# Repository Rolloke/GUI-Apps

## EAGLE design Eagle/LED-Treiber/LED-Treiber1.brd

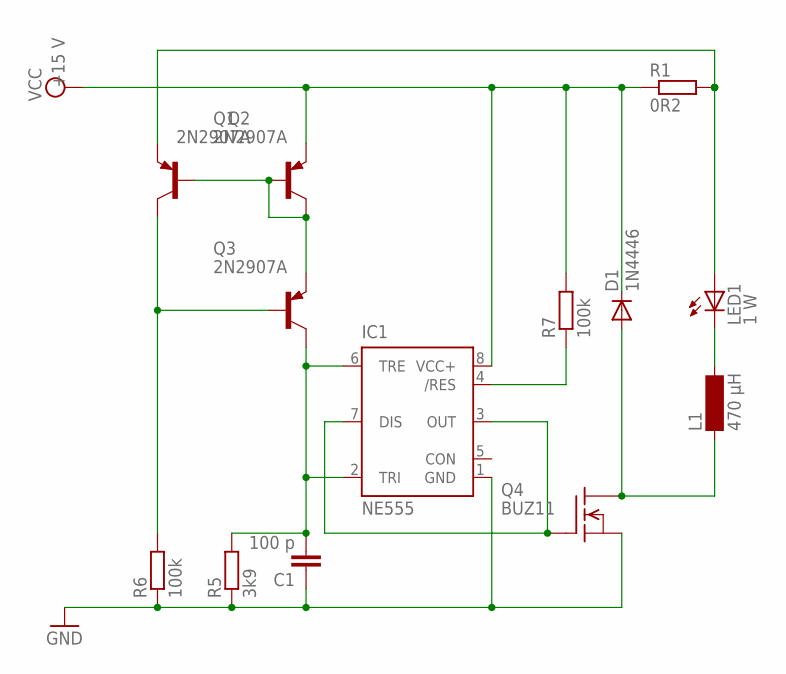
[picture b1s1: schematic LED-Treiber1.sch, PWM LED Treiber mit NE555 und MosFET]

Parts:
C1: 100 p; C2.5-3
D1: 1N4446; DO35-10
IC1: NE555; DIL-08
L1: 470 µH; MS85
LED1: 1 W; LED5MM
Q1, Q2, Q3: 2N2907A; TO18
Q4: BUZ11; TO220
R1: 0R2; 0207/10
R5: 3k9; 0207/10
R6, R7: 100k; 0207/10

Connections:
GND: C1.1, IC1.1 (GND), Q4.3 (S), R5.1, R6.1
unnamed: Q1.2 (B), Q1.3 (C), Q2.2 (B), Q3.1 (E)
unnamed: C1.2, IC1.2 (TRI), IC1.6 (TRE), Q3.3 (C), R5.2
unnamed: Q2.3 (C), Q3.2 (B), R6.2
unnamed: IC1.3 (OUT), IC1.7 (DIS), Q4.1 (G)
unnamed: IC1.4 (/RES), R7.1
unnamed: D1.A, L1.1, Q4.2 (D)
unnamed: L1.2, LED1.K (C)
unnamed: LED1.A, Q2.1 (E), R1.2
VCC: D1.C, IC1.8 (VCC+), Q1.1 (E), R1.1, R7.2

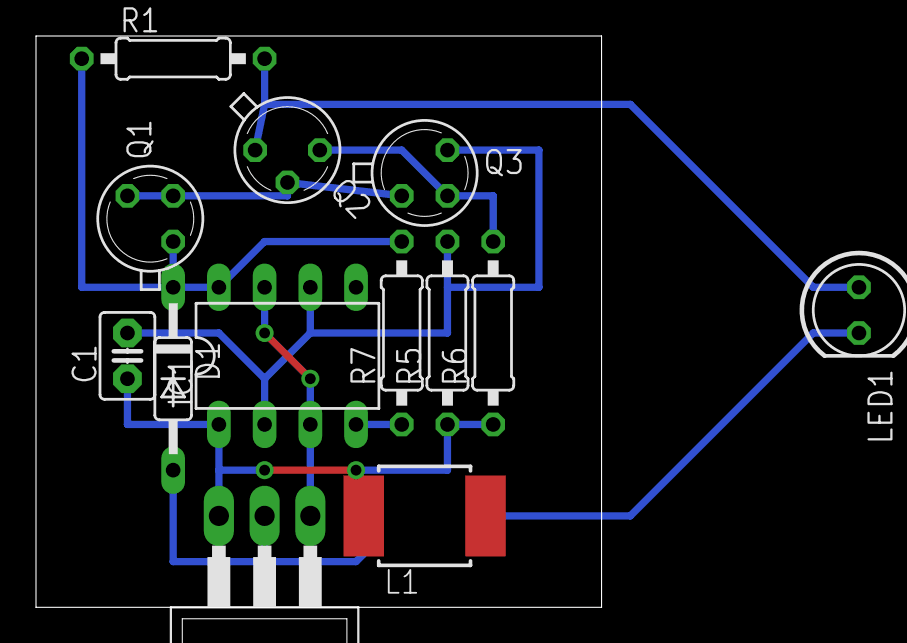
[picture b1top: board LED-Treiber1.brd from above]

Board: 2 copper layers, 31.4 x 31.7 mm, 13 parts (0 on the bottom side), 10 nets.

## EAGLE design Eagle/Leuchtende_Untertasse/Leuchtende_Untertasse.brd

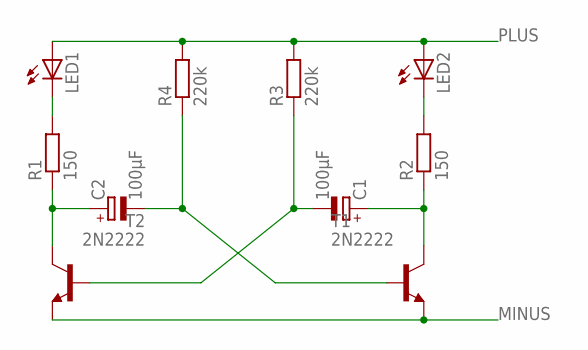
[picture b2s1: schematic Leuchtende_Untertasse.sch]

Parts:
C1, C2: 100µF; E2,5-5
LED1, LED2: LED5MM
R1, R2: 150; 0204/7
R3, R4: 220k; 0204/7
T1, T2: 2N2222; TO18

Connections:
MINUS: T1.1 (E), T2.1 (E)
unnamed: C2.+, R1.1, T2.3 (C)
unnamed: C1.+, R2.1, T1.3 (C)
unnamed: C1.-, R3.1, T2.2 (B)
unnamed: C2.-, R4.1, T1.2 (B)
unnamed: LED2.K (C), R2.2
unnamed: LED1.K (C), R1.2
PLUS: LED1.A, LED2.A, R3.2, R4.2

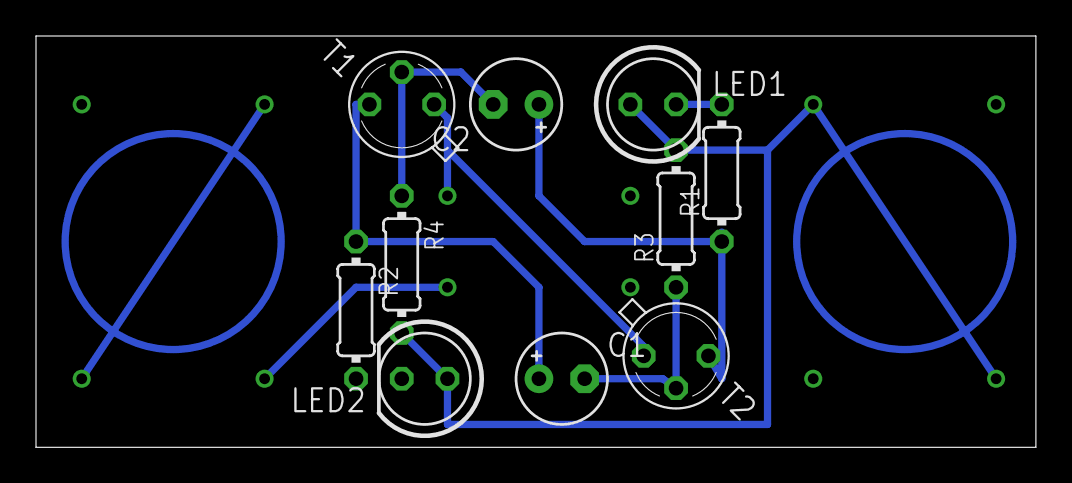
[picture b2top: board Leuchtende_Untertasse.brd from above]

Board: 2 copper layers, 55.5 x 22.8 mm, 10 parts (0 on the bottom side), 8 nets.

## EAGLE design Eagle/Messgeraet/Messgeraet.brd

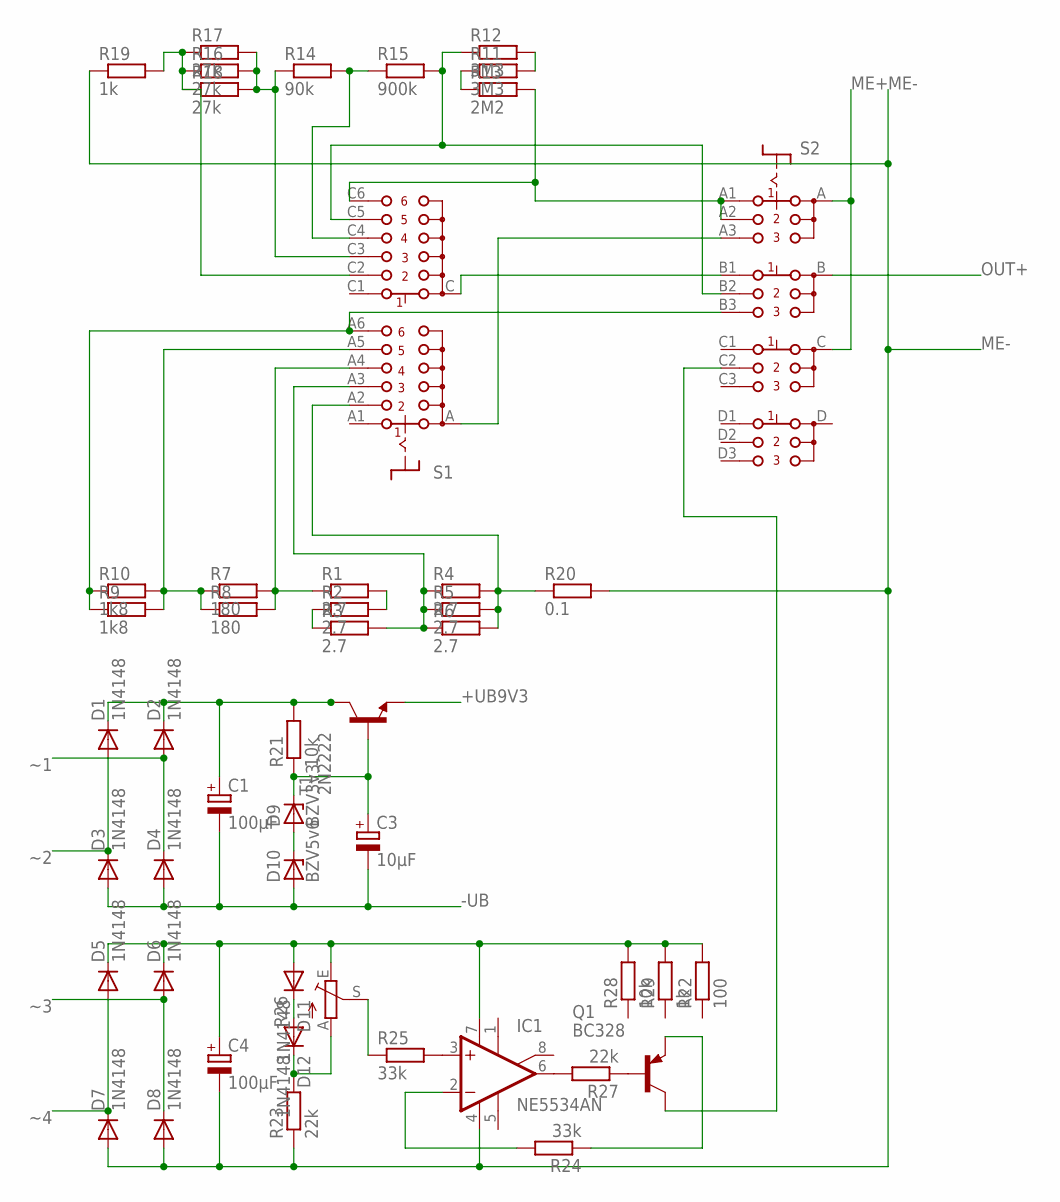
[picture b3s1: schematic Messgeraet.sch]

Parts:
C1, C4: 100µF; E5-10,5
C3: 10µF; E5-10,5
D1, D2, D3, D4, D5, D6, D7, D8, D11, D12: 1N4148; DO35-7
D9: BZV3v3; DO34Z7
D10: BZV5v6; DO34Z7
IC1: NE5534AN; DIL08
Q1: BC328; TO92-EBC
R1, R2, R3, R4, R5, R6: 2.7; 0617/17
R7, R8: 180; 0309/12
R9, R10: 1k8; 0309/10
R11, R12: 3M3; 0309/12
R13: 2M2; 0411/15
R14: 90k; 0411/15
R15: 900k; 0309V
R16, R17, R18: 27k; 0309/12
R19, R29: 1k; 0309/10
R20: 0.1; VTA52
R21, R28: 10k; 0309/10
R22: 100; 0309/10
R23, R27: 22k; 0309/10
R24, R25: 33k; 0309/10
R26: TRIM_EU-RJ9W; RJ9W
S1: CK102X06
S2: CK104X03
T1: 2N2222; TO18

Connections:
+UB9V3: T1.1 (E)
-UB: C1.-, C3.-, D3.A, D4.A, D10.A
ME+: S2.A, S2.C
ME-: C4.-, D7.A, D8.A, IC1.4 (V-), R19.1, R20.2, R23.1
unnamed: R7.1, R8.1, R9.2, R10.2, S1.A5
unnamed: S1.A, S2.A3
unnamed: R1.1, R7.2, R8.2, S1.A4
unnamed: R9.1, R10.1, S1.A6, S2.B3
unnamed: R1.2, R2.2
unnamed: R2.1, R3.1
unnamed: R3.2, R4.1, R5.1, R6.1, S1.A3
unnamed: R4.2, R5.2, R6.2, R20.1, S1.A2
unnamed: R14.1, R16.2, R17.2, R18.2, S1.C3
unnamed: R16.1, R17.1, R18.1, R19.2, S1.C2
unnamed: D12.C, R23.2, R26.A
unnamed: R14.2, R15.1, S1.C4
unnamed: R12.1, R15.2, S1.C5, S2.B2
unnamed: R11.2, R12.2
unnamed: R11.1, R13.1
unnamed: R13.2, S1.C6, S2.A1, S2.A2
unnamed: S1.C, S2.B1
unnamed: Q1.C, S2.C2
unnamed: IC1.6 (OUT), R27.2
unnamed: C1.+, D1.C, D2.C, R21.2, T1.3 (C)
unnamed: Q1.B, R27.1
unnamed: D11.C, D12.A
unnamed: Q1.E, R24.1
unnamed: C4.+, D5.C, D6.C, D11.A, IC1.7 (V+), R22.2, R26.E, R28.2, R29.2
unnamed: R25.1, R26.S
unnamed: D9.A, D10.C
unnamed: C3.+, D9.C, R21.1, T1.2 (B)
unnamed: IC1.2 (-IN), R24.2
unnamed: IC1.3 (+IN), R25.2
OUT+: S2.B
~1: D2.A, D4.C
~2: D1.A, D3.C
~3: D6.A, D8.C
~4: D5.A, D7.C

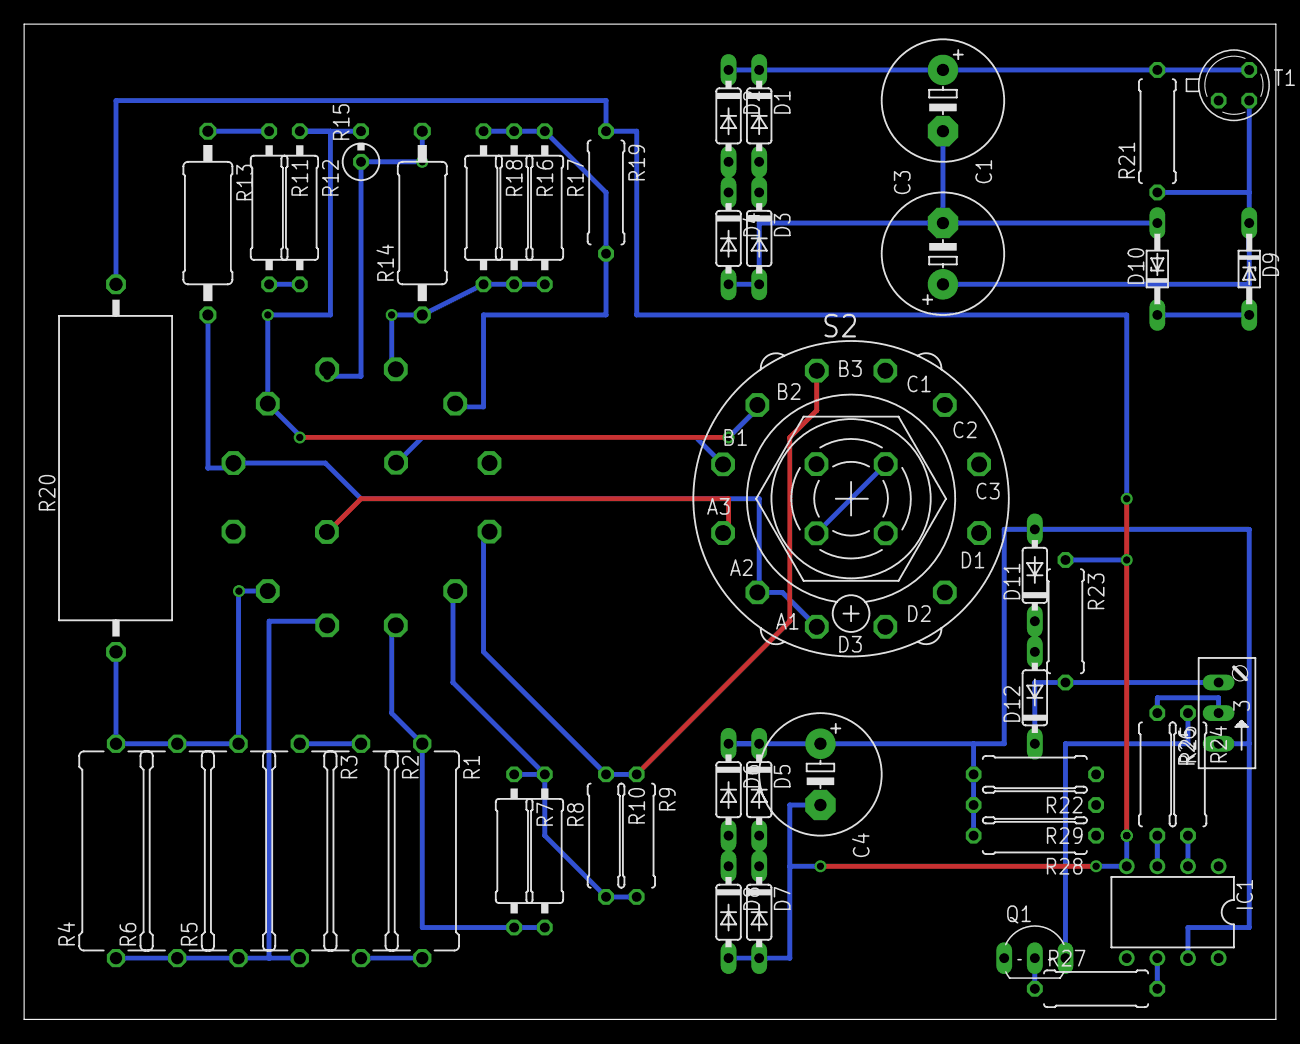
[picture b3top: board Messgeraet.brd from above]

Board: 2 copper layers, 103.8 x 82.5 mm, 49 parts (1 on the bottom side), 36 nets.

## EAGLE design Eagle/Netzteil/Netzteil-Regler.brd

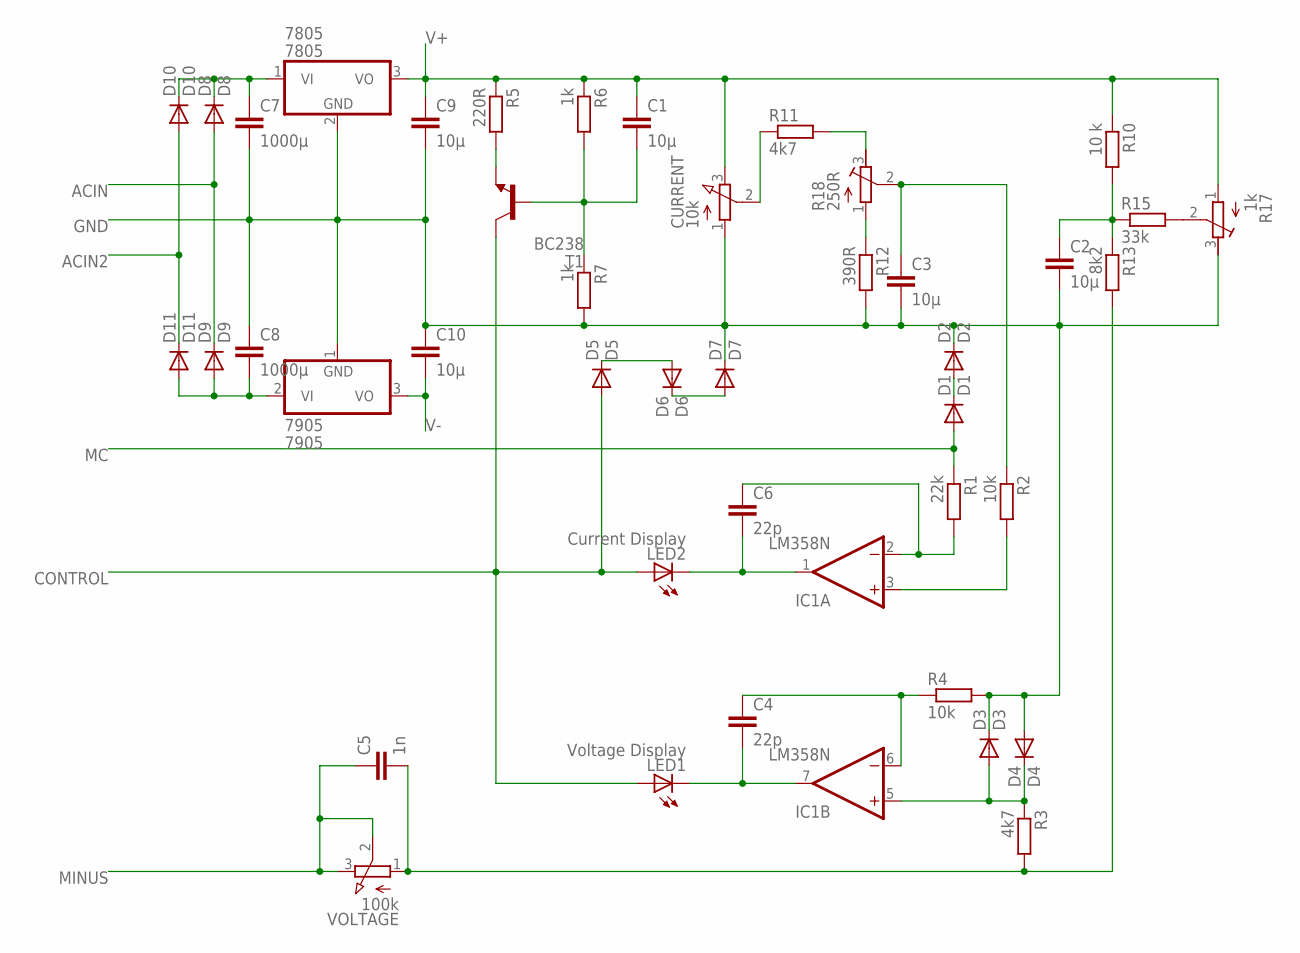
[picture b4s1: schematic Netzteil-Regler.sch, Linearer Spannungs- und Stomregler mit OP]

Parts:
7805: 7805; TO220V
7905: 7905; TO220V
C1, C2, C3, C9, C10: 10µ; C2.5-5
C4, C6: 22p; C5B4.5
C5: 1n; C5B4.5
C7, C8: 1000µ; C10B6
CURRENT: 10k; 3RP/1610N
D1: D1; DO35-10
D2: D2; DO35-10
D3: D3; DO35-10
D4: D4; DO35-10
D5: D5; DO35-10
D6: D6; DO35-10
D7: D7; DO35-10
D8: D8; DO41-10
D9: D9; DO41-10
D10: D10; DO41-10
D11: D11; DO41-10
IC1: LM358N; DIL08
LED1: Voltage Display; LED5MM
LED2: Current Display; LED5MM
R1: 22k; 0207/10
R2, R4: 10k; 0207/10
R3, R11: 4k7; 0207/10
R5: 220R; 0207/10
R6, R7: 1k; 0207/10
R10: 10 k; 0207/10
R12: 390R; 0207/10
R13: 8k2; 0207/10
R15: 33k; 0207/10
R17: 1k; RTRIM3296W
R18: 250R; RTRIM3296W
T1: BC238; TO92-CBE
VOLTAGE: 100k; 3RP/1610N

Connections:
ACIN: D8.A, D9.C
ACIN2: D10.A, D11.C
B: C1.2, R6.2, R7.1, T1.B
CONTROL: D5.A, LED1.A, LED2.A, T1.C
E: R5.2, T1.E
GND: 7805.2 (GND), 7905.1 (GND), C2.2, C3.2, C7.2, C8.1, C9.2, C10.1, CURRENT.1 (A), D2.C, D3.C, D4.A, D7.C, R4.2, R7.2, R12.2, R17.3 (A)
MC: D1.A, R1.1
MINUS: C5.1, VOLTAGE.2 (S), VOLTAGE.3 (E)
unnamed: R11.2, R18.3 (A)
unnamed: C3.1, R2.1, R18.2 (S)
unnamed: R12.1, R18.1 (E)
unnamed: D1.C, D2.A
unnamed: C2.1, R10.2, R13.1, R15.1
unnamed: CURRENT.2 (S), R11.1
unnamed: R15.2, R17.2 (S)
unnamed: IC1.3 (+IN), R2.2
unnamed: C6.1, IC1.2 (-IN), R1.2
unnamed: 7805.1 (VI), C7.1, D8.C, D10.C
unnamed: D5.C, D6.A
unnamed: D6.C, D7.A
unnamed: C4.2, IC1.7 (OUT), LED1.K (C)
unnamed: C4.1, IC1.6 (-IN), R4.1
unnamed: D3.A, D4.C, IC1.5 (+IN), R3.1
unnamed: C5.2, R3.2, R13.2, VOLTAGE.1 (A)
unnamed: C6.2, IC1.1 (OUT), LED2.K (C)
unnamed: 7905.2 (VI), C8.2, D9.A, D11.A
V+: 7805.3 (VO), C1.1, C9.1, CURRENT.3 (E), IC1.8 (V+), R5.1, R6.1, R10.1, R17.1 (E)
V-: 7905.3 (VO), C10.2, IC1.4 (V-)

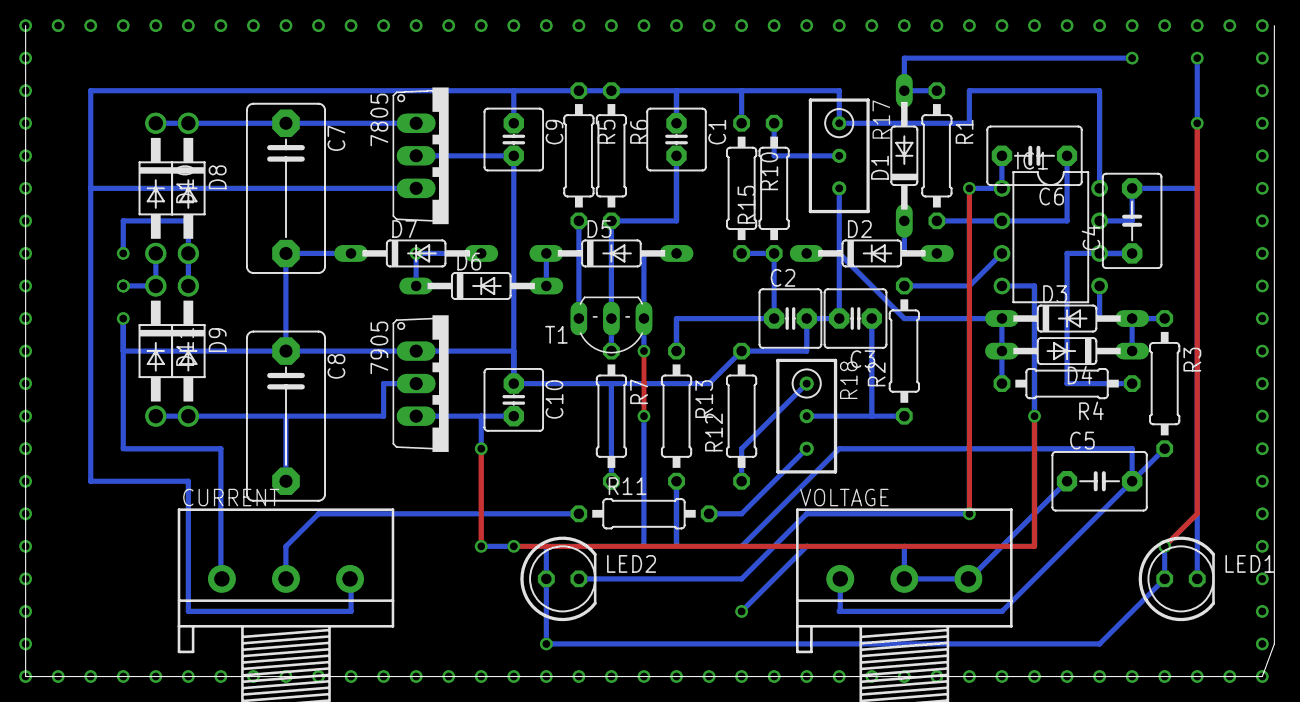
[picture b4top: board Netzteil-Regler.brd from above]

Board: 2 copper layers, 97.5 x 50.8 mm, 43 parts (0 on the bottom side), 28 nets.

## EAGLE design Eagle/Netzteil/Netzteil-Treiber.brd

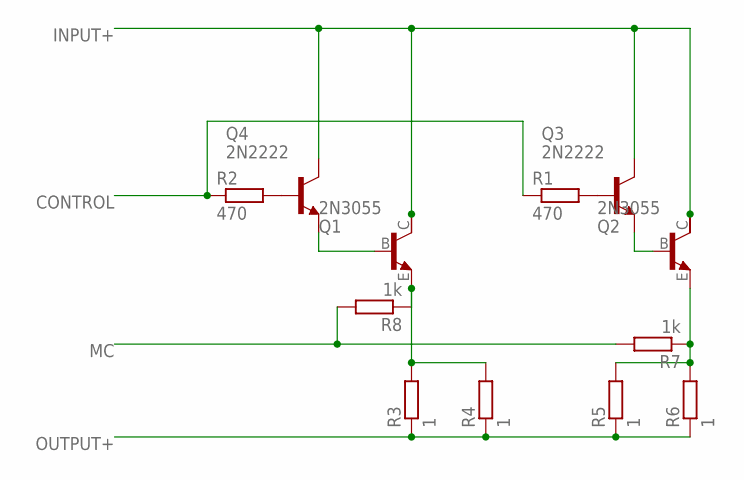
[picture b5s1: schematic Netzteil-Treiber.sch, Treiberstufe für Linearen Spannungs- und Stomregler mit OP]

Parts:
Q1, Q2: 2N3055; TO3
Q3, Q4: 2N2222; TO18
R1, R2: 470; 0207/12
R3, R4, R5, R6: 1; 0207/12
R7, R8: 1k; 0207/12

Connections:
CONTROL: R1.1, R2.1
INPUT+: Q1.C, Q2.C, Q3.3 (C), Q4.3 (C)
MC: R7.2, R8.2
unnamed: Q3.2 (B), R1.2
unnamed: Q4.2 (B), R2.2
unnamed: Q1.E, R3.2, R4.2, R8.1
unnamed: Q1.B, Q4.1 (E)
unnamed: Q2.B, Q3.1 (E)
unnamed: Q2.E, R5.2, R6.2, R7.1
OUTPUT+: R3.1, R4.1, R5.1, R6.1

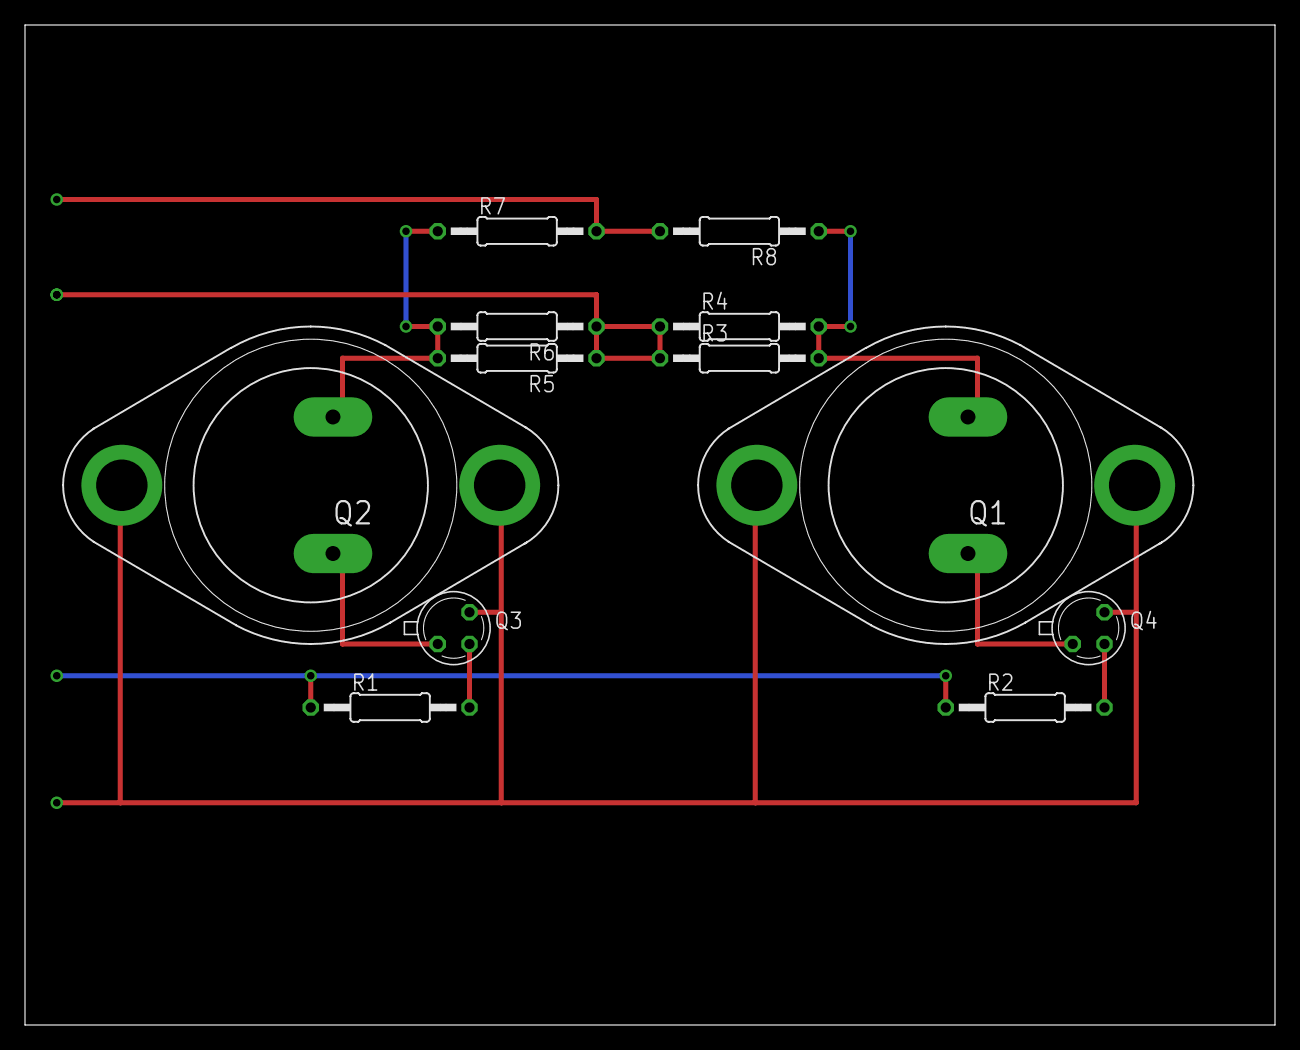
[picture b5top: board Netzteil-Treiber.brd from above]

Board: 2 copper layers, 100.0 x 80.0 mm, 12 parts (0 on the bottom side), 10 nets.
